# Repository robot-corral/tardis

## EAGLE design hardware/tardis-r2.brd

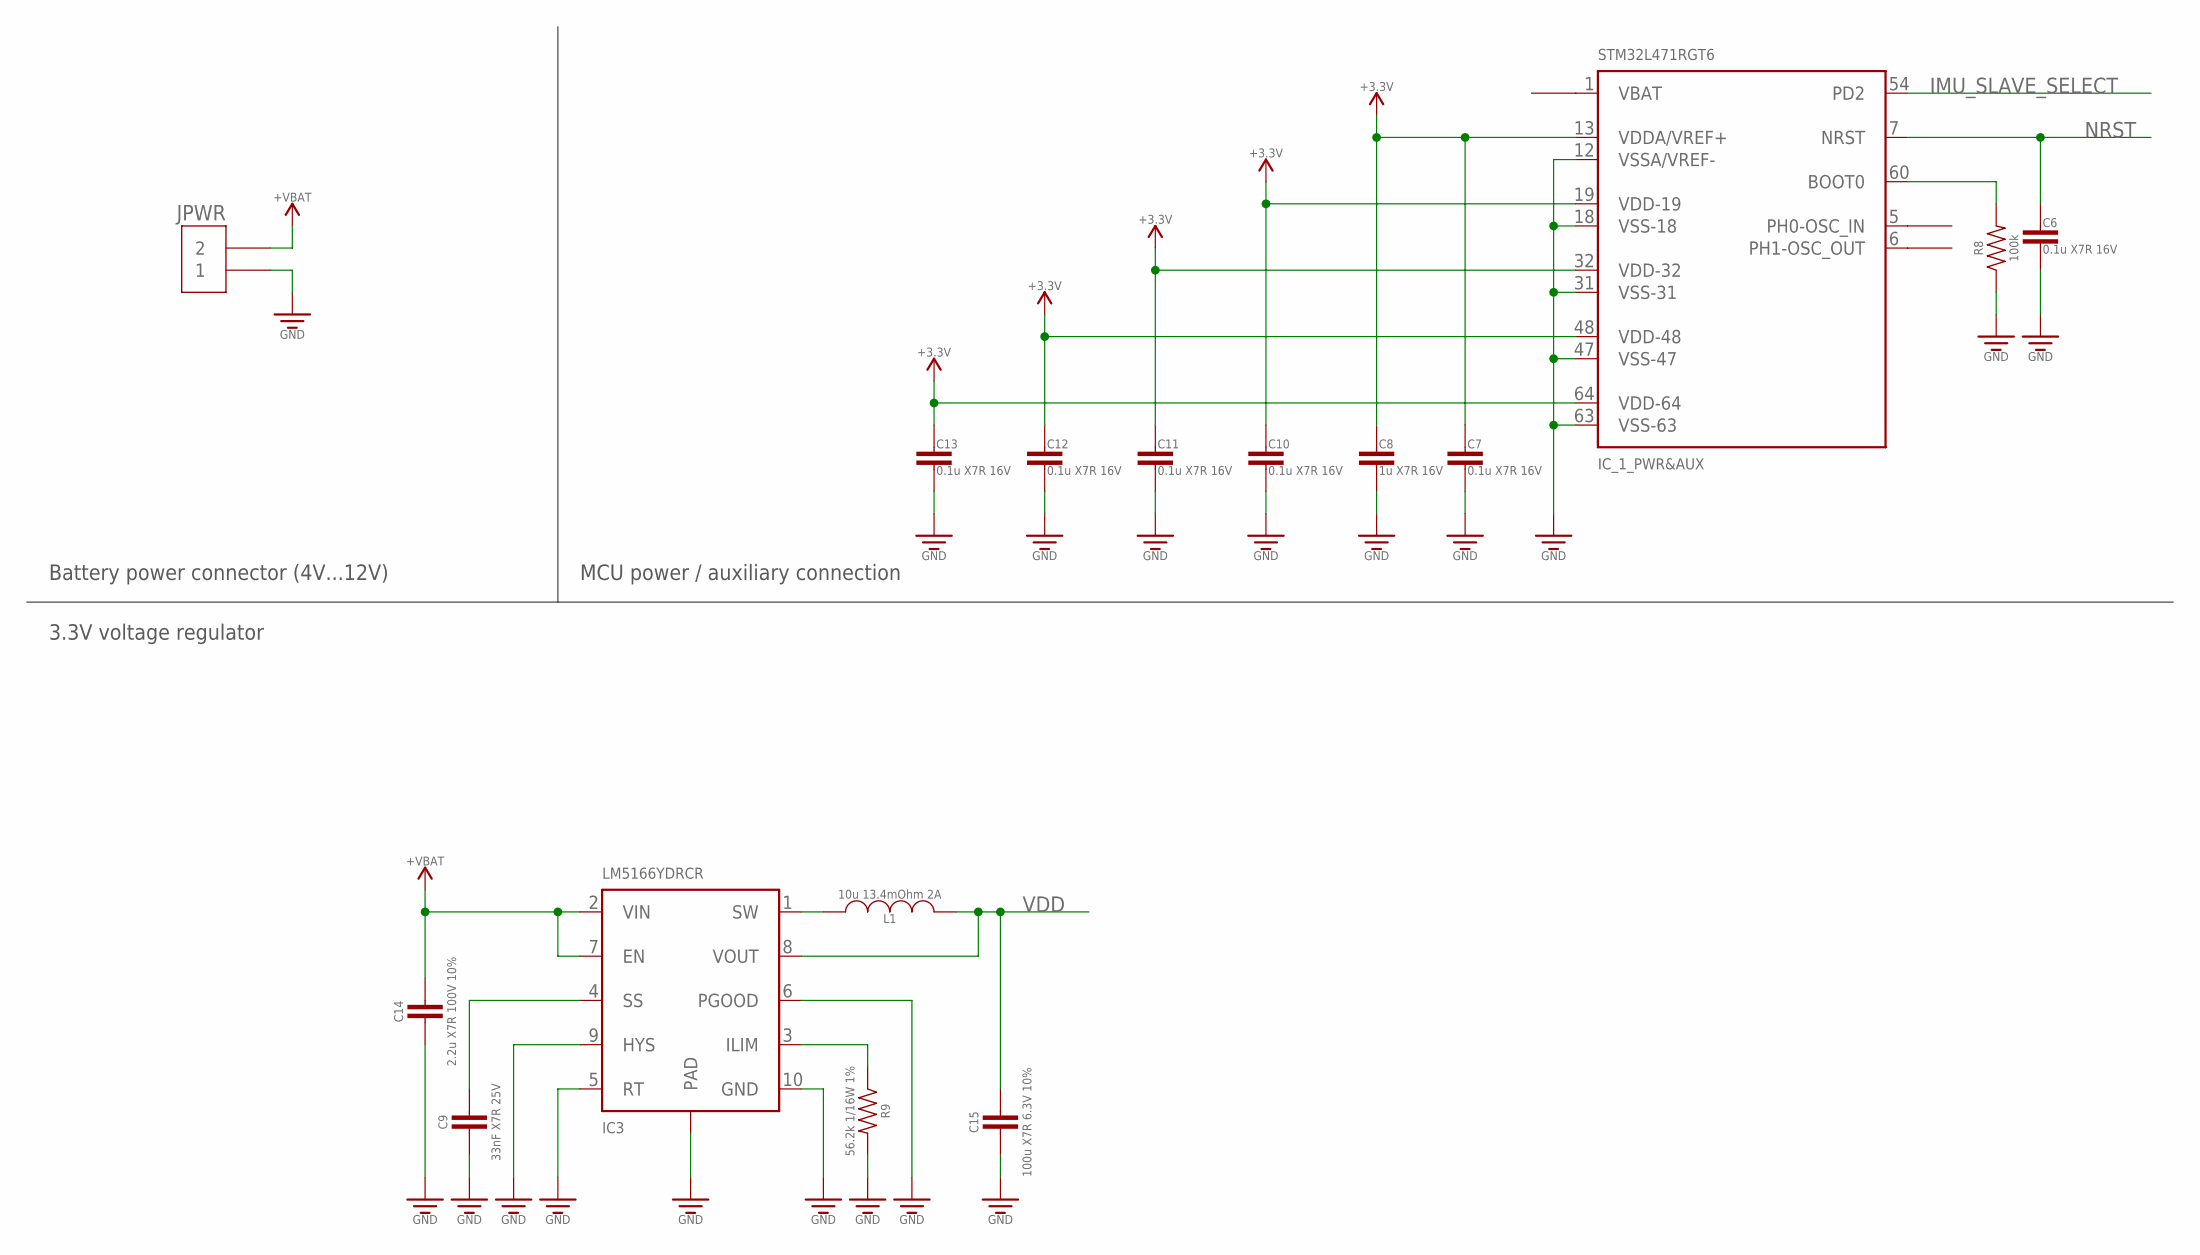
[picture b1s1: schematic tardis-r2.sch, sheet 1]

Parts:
C6, C7, C10, C11, C12, C13: 0.1u X7R 16V; CAPACITOR-0603
C8: 1u X7R 16V; CAPACITOR-0603
C9: 33nF X7R 25V; CAPACITOR-0402
C14: 2.2u X7R 100V 10%; CAPACITOR-1206
C15: 100u X7R 6.3V 10%; CAPACITOR-1206
IC3: LM5166YDRCR; VSON-10-0.5MM-PAD
IC_1: STM32L471RGT6; LQFP64_10X10
JPWR: WURTH_691103110002
L1: 10u 13.4mOhm 2A; INDUCTOR-WE-74477710
R8: 100k; RESISTOR-0603
R9: 56.2k 1/16W 1%; RESISTOR-0402

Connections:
BOOT0: IC_1.60 (BOOT0), R8.P$2 (2)
GND: C6.2, C7.2, C8.2, C9.P$2 (2), C10.2, C11.2, C12.2, C13.2, C14.P$2 (2), C15.P$2 (2), IC3.5 (RT), IC3.6 (PGOOD), IC3.9 (HYS), IC3.10 (GND), IC3.PAD, IC_1.12 (VSSA/VREF-), IC_1.18 (VSS-18), IC_1.31 (VSS-31), IC_1.47 (VSS-47), IC_1.63 (VSS-63), JPWR.1, R8.P$1 (1), R9.P$2 (2); also elsewhere on the board
ILIM: IC3.3 (ILIM), R9.P$1 (1)
IMU_SLAVE_SELECT: IC_1.54 (PD2); also elsewhere on the board
NRST: C6.1, IC_1.7 (NRST); also elsewhere on the board
SS: C9.P$1 (1), IC3.4 (SS)
SW: IC3.1 (SW), L1.P$1
VBAT: C14.P$1 (1), IC3.2 (VIN), IC3.7 (EN), JPWR.2
VDD: C7.1, C8.1, C10.1, C11.1, C12.1, C13.1, C15.P$1 (1), IC3.8 (VOUT), IC_1.13 (VDDA/VREF+), IC_1.19 (VDD-19), IC_1.32 (VDD-32), IC_1.48 (VDD-48), IC_1.64 (VDD-64), L1.P$2; also elsewhere on the board

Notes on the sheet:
Battery power connector (4V...12V)
MCU power / auxiliary connection
3.3V voltage regulator

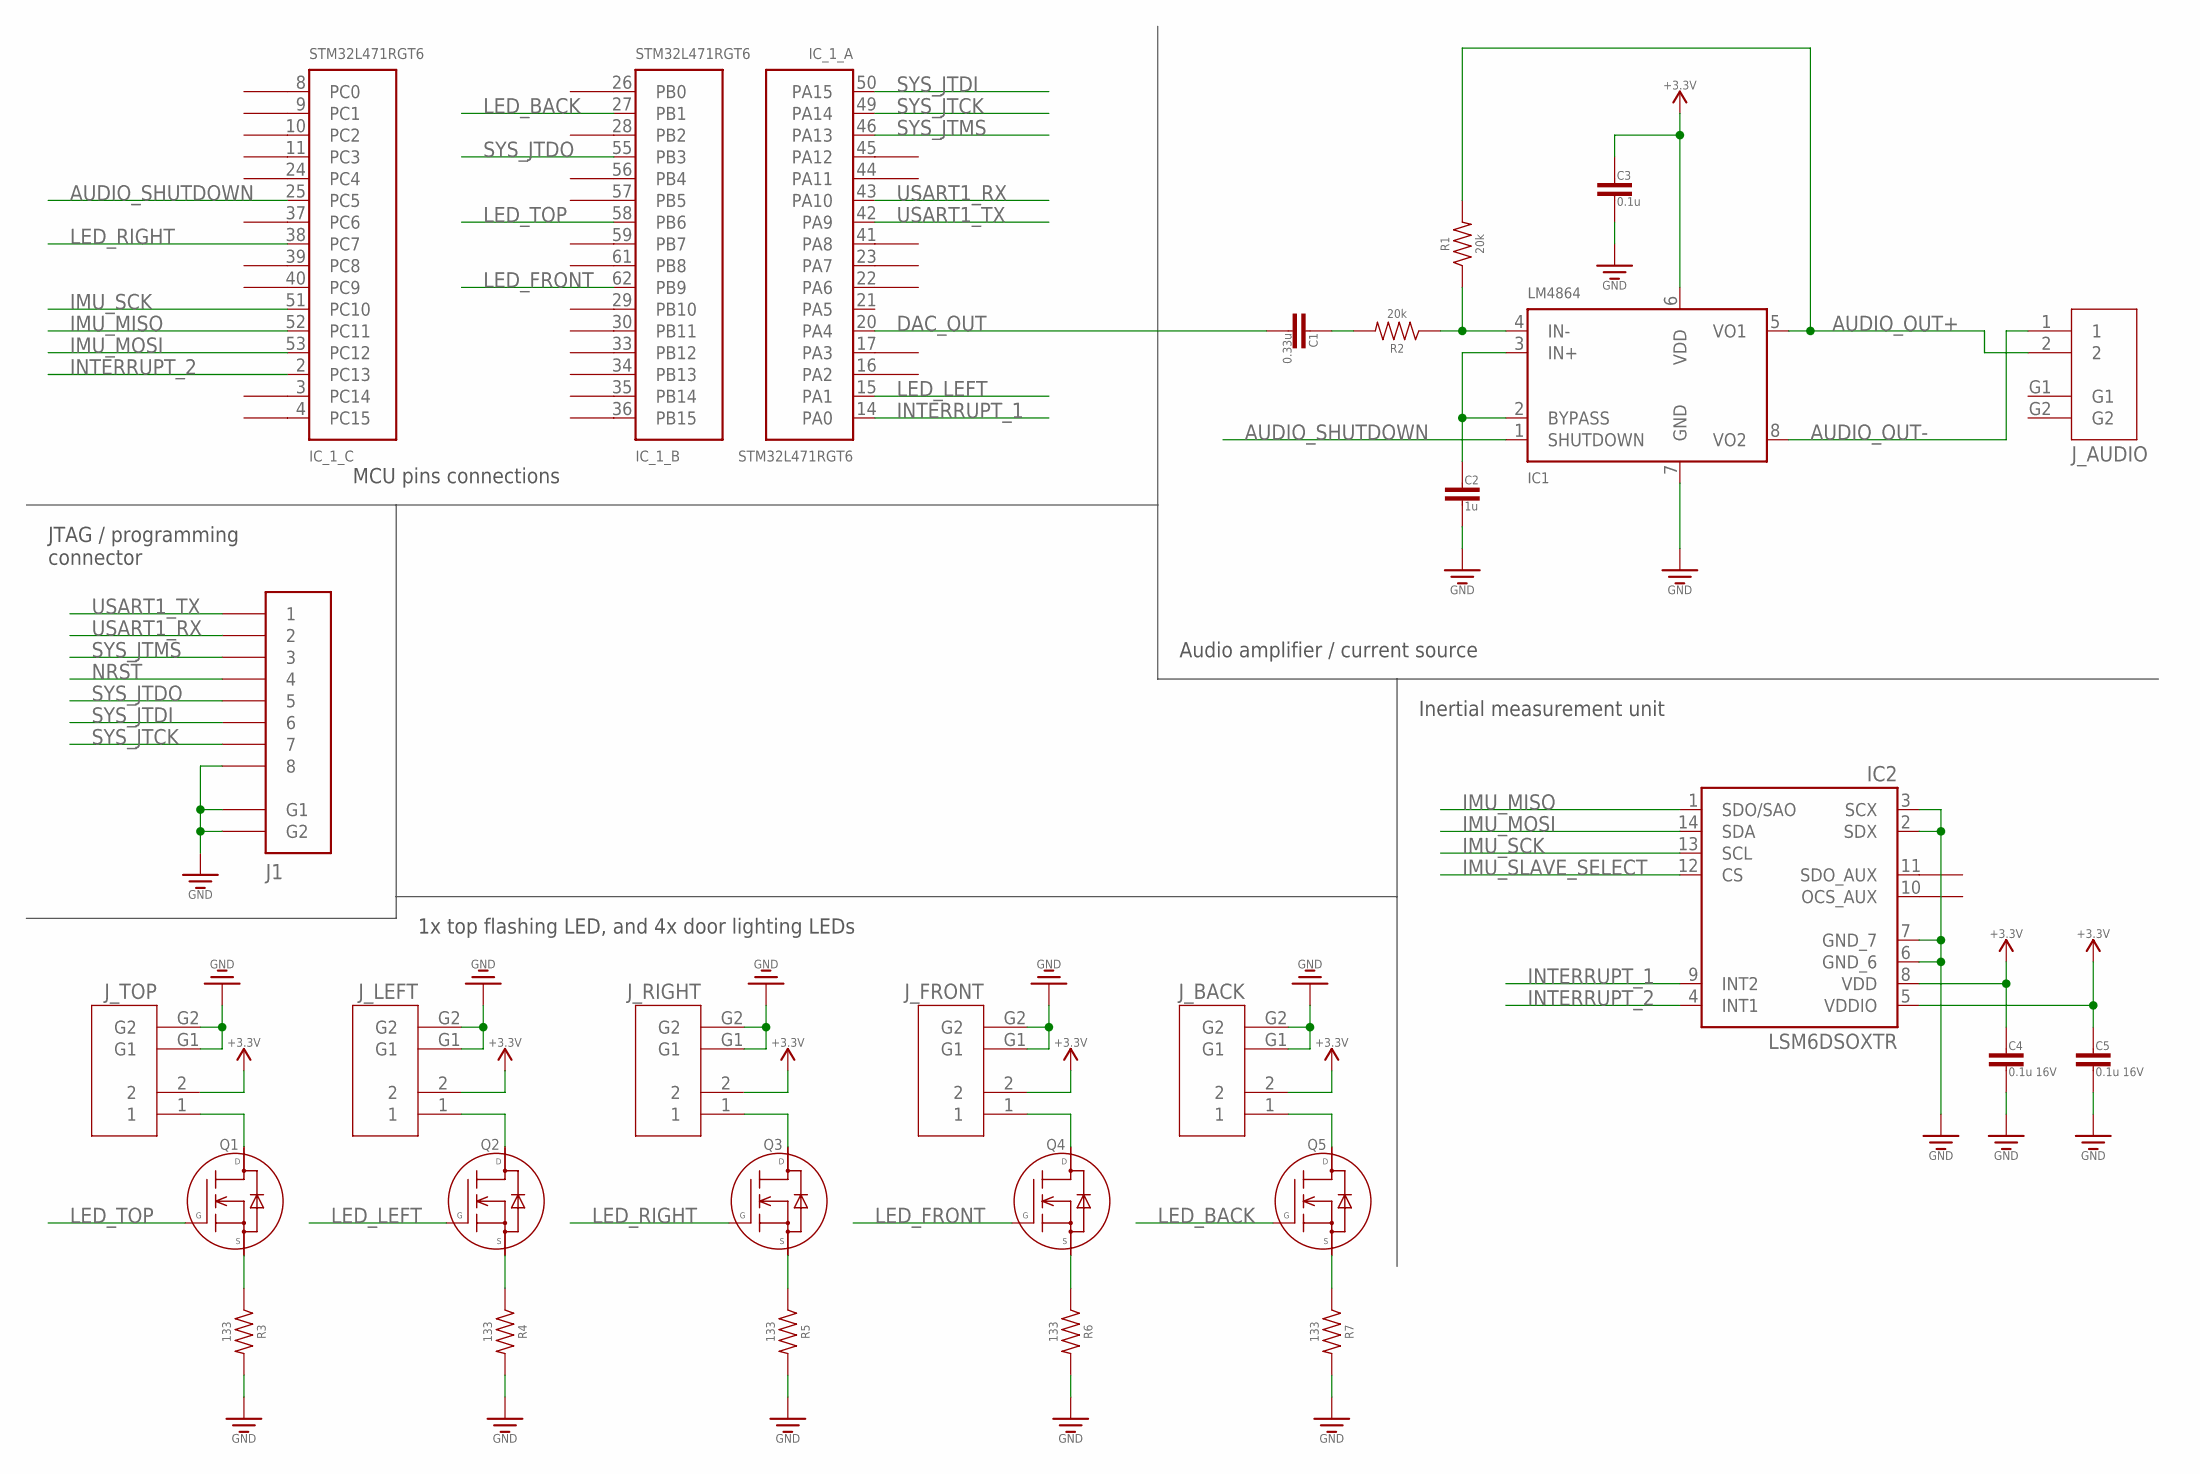
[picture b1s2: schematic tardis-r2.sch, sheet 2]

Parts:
C1: 0.33u; CAPACITOR-0805
C2: 1u; CAPACITOR-0805
C3: 0.1u; CAPACITOR-0805
C4, C5: 0.1u 16V; CAPACITOR-0603
IC1: LM4864; SOIC-8
IC2: LSM6DSOXTR; LGA-14L
IC_1: STM32L471RGT6; LQFP64_10X10
J1: MOLEX-53261-0871
J_AUDIO: MOLEX-502382-02XX
J_BACK: MOLEX-502382-02XX
J_FRONT: MOLEX-502382-02XX
J_LEFT: MOLEX-502382-02XX
J_RIGHT: MOLEX-502382-02XX
J_TOP: MOLEX-502382-02XX
Q1, Q2, Q3, Q4, Q5: 2N7002; SOT-23
R1, R2: 20k; RESISTOR-0805
R3, R4, R5, R6, R7: 133; RESISTOR-0805

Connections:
AUDIO_OUT+: IC1.5 (VO1), J_AUDIO.2, R1.2
AUDIO_OUT-: IC1.8 (VO2), J_AUDIO.1
AUDIO_SHUTDOWN: IC1.1 (SHUTDOWN), IC_1.25 (PC5)
DAC_OUT: C1.2, IC_1.20 (PA4)
GND: C2.2, C3.2, C4.2, C5.2, IC1.7 (GND), IC2.2 (SDX), IC2.3 (SCX), IC2.6 (GND_6), IC2.7 (GND_7), J1.8, J1.G1, J1.G2, J_BACK.G1, J_BACK.G2, J_FRONT.G1, J_FRONT.G2, J_LEFT.G1, J_LEFT.G2, J_RIGHT.G1, J_RIGHT.G2, J_TOP.G1, J_TOP.G2, R3.2, R4.2, R5.2, R6.2, R7.2; also elsewhere on the board
IMU_MISO: IC2.1 (SDO/SAO), IC_1.52 (PC11)
IMU_MOSI: IC2.14 (SDA), IC_1.53 (PC12)
IMU_SCK: IC2.13 (SCL), IC_1.51 (PC10)
IMU_SLAVE_SELECT: IC2.12 (CS); also elsewhere on the board
INTERRUPT_1: IC2.9 (INT2), IC_1.14 (PA0)
INTERRUPT_2: IC2.4 (INT1), IC_1.2 (PC13)
LED_BACK: IC_1.27 (PB1), Q5.P$2 (GATE)
LED_FRONT: IC_1.62 (PB9), Q4.P$2 (GATE)
LED_LEFT: IC_1.15 (PA1), Q2.P$2 (GATE)
LED_RIGHT: IC_1.38 (PC7), Q3.P$2 (GATE)
LED_TOP: IC_1.58 (PB6), Q1.P$2 (GATE)
unnamed: C2.1, IC1.2 (BYPASS), IC1.3 (IN+)
unnamed: Q1.P$3 (SOURCE), R3.1
unnamed: IC1.4 (IN-), R1.1, R2.1
unnamed: C1.1, R2.2
unnamed: J_TOP.1, Q1.P$1 (DRAIN)
unnamed: Q2.P$3 (SOURCE), R4.1
unnamed: J_LEFT.1, Q2.P$1 (DRAIN)
unnamed: Q3.P$3 (SOURCE), R5.1
unnamed: J_RIGHT.1, Q3.P$1 (DRAIN)
unnamed: Q4.P$3 (SOURCE), R6.1
unnamed: J_FRONT.1, Q4.P$1 (DRAIN)
unnamed: Q5.P$3 (SOURCE), R7.1
unnamed: J_BACK.1, Q5.P$1 (DRAIN)
NRST: J1.4; also elsewhere on the board
SYS_JTCK: IC_1.49 (PA14), J1.7
SYS_JTDI: IC_1.50 (PA15), J1.6
SYS_JTDO: IC_1.55 (PB3), J1.5
SYS_JTMS: IC_1.46 (PA13), J1.3
USART1_RX: IC_1.43 (PA10), J1.2
USART1_TX: IC_1.42 (PA9), J1.1
VDD: C3.1, C4.1, C5.1, IC1.6 (VDD), IC2.5 (VDDIO), IC2.8 (VDD), J_BACK.2, J_FRONT.2, J_LEFT.2, J_RIGHT.2, J_TOP.2; also elsewhere on the board

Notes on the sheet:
1x top flashing LED, and 4x door lighting LEDs
JTAG / programming connector
MCU pins connections
Audio amplifier / current source
Inertial measurement unit

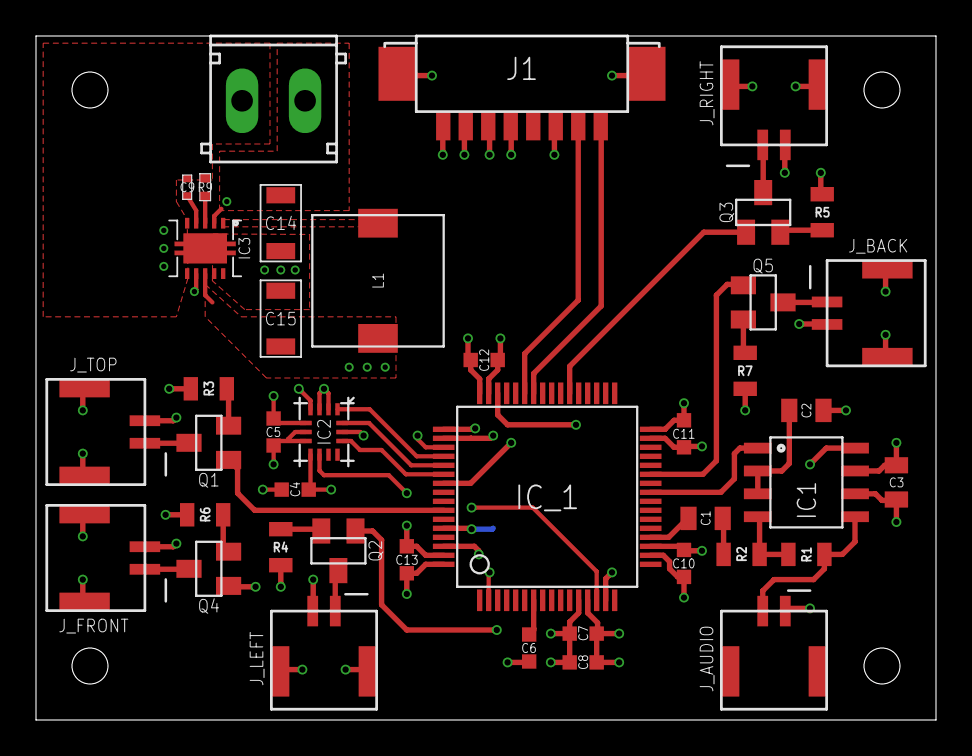
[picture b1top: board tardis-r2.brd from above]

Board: 4 copper layers, 50.0 x 38.0 mm, 42 parts (1 on the bottom side), 42 nets.

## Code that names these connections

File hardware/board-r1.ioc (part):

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Mcu.Name=STM32L471R(E-G)Tx
Mcu.Package=LQFP64
Mcu.UserName=STM32L471RGTx
PA0.Mode=SYS_WakeUp0
PA0.Signal=SYS_WKUP1
PA1.Signal=S_TIM2_CH2
PA10.Mode=Asynchronous
PA10.Signal=USART1_RX
PA13\ (JTMS-SWDIO).Mode=JTAG_5_pins
PA13\ (JTMS-SWDIO).Signal=SYS_JTMS-SWDIO
PA14\ (JTCK-SWCLK).Mode=JTAG_5_pins
PA14\ (JTCK-SWCLK).Signal=SYS_JTCK-SWCLK
PA15\ (JTDI).Mode=JTAG_5_pins
PA15\ (JTDI).Signal=SYS_JTDI
PA4.Signal=COMP_DAC11_group
PA5.Signal=GPIO_Output
PA9.Mode=Asynchronous
PA9.Signal=USART1_TX
PB1.Signal=S_TIM3_CH4
PB3\ (JTDO-TRACESWO).Mode=JTAG_5_pins
PB3\ (JTDO-TRACESWO).Signal=SYS_JTDO-SWO
PB4\ (NJTRST).Mode=JTAG_5_pins
PB4\ (NJTRST).Signal=SYS_JTRST
PB6.Signal=S_TIM4_CH1
PB9.Signal=S_TIM4_CH4
PC10.Mode=Full_Duplex_Master
PC10.Signal=SPI3_SCK
PC11.Mode=Full_Duplex_Master
PC11.Signal=SPI3_MISO
PC12.Mode=Full_Duplex_Master
PC12.Signal=SPI3_MOSI
PC13.Mode=SYS_WakeUp1
PC13.Signal=SYS_WKUP2
PC7.Signal=S_TIM3_CH2
PD2.Signal=GPIO_Output
RCC.HSE_VALUE=8000000
board=custom

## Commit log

2019-08-08 added hardware projects
2019-08-08 added template software project
2019-08-15 - added revision description for eagle pcb - added full sound playback for tardis
2019-08-16 - fixed sound (should be a bit clearer) - top light now flashes with sound (sort of)
2019-08-17 - top light will be off when device powers on
2019-11-15 added code which makes sound and light work
